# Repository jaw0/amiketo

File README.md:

tiny, low power, ARM-based board

* 35mm x 69mm
* breadboard friendly pinout

hardware:

* STM32F411
  * 96 MHz Cortex M4F
  * 100 uA / MHz
  * 10 analog inputs
  * 10 digital inputs
  * 10 digital outputs
  *  8 PWM outputs
  * i2c, spi, uart, usb
  * real-time-clock
  * board compat with most 48pin STM32s (eg. F103, L152, L072)
* micro SD card
* audio speaker
* OLED display
* AD5062 programmable battery charger
  * configurable charge current
  * configurable USB current
  * configurable charging parameters
* MAX17048 battery fuel gauge

software:

* can (will eventually) run open-source:
  * python
  * javascript
  * mbed
  * .NET
  * arduino
* comes with battery charger + data-logger
* write your own code

other:

* RoHS, lead-free
* fat-free, sugar-free, gluten-free

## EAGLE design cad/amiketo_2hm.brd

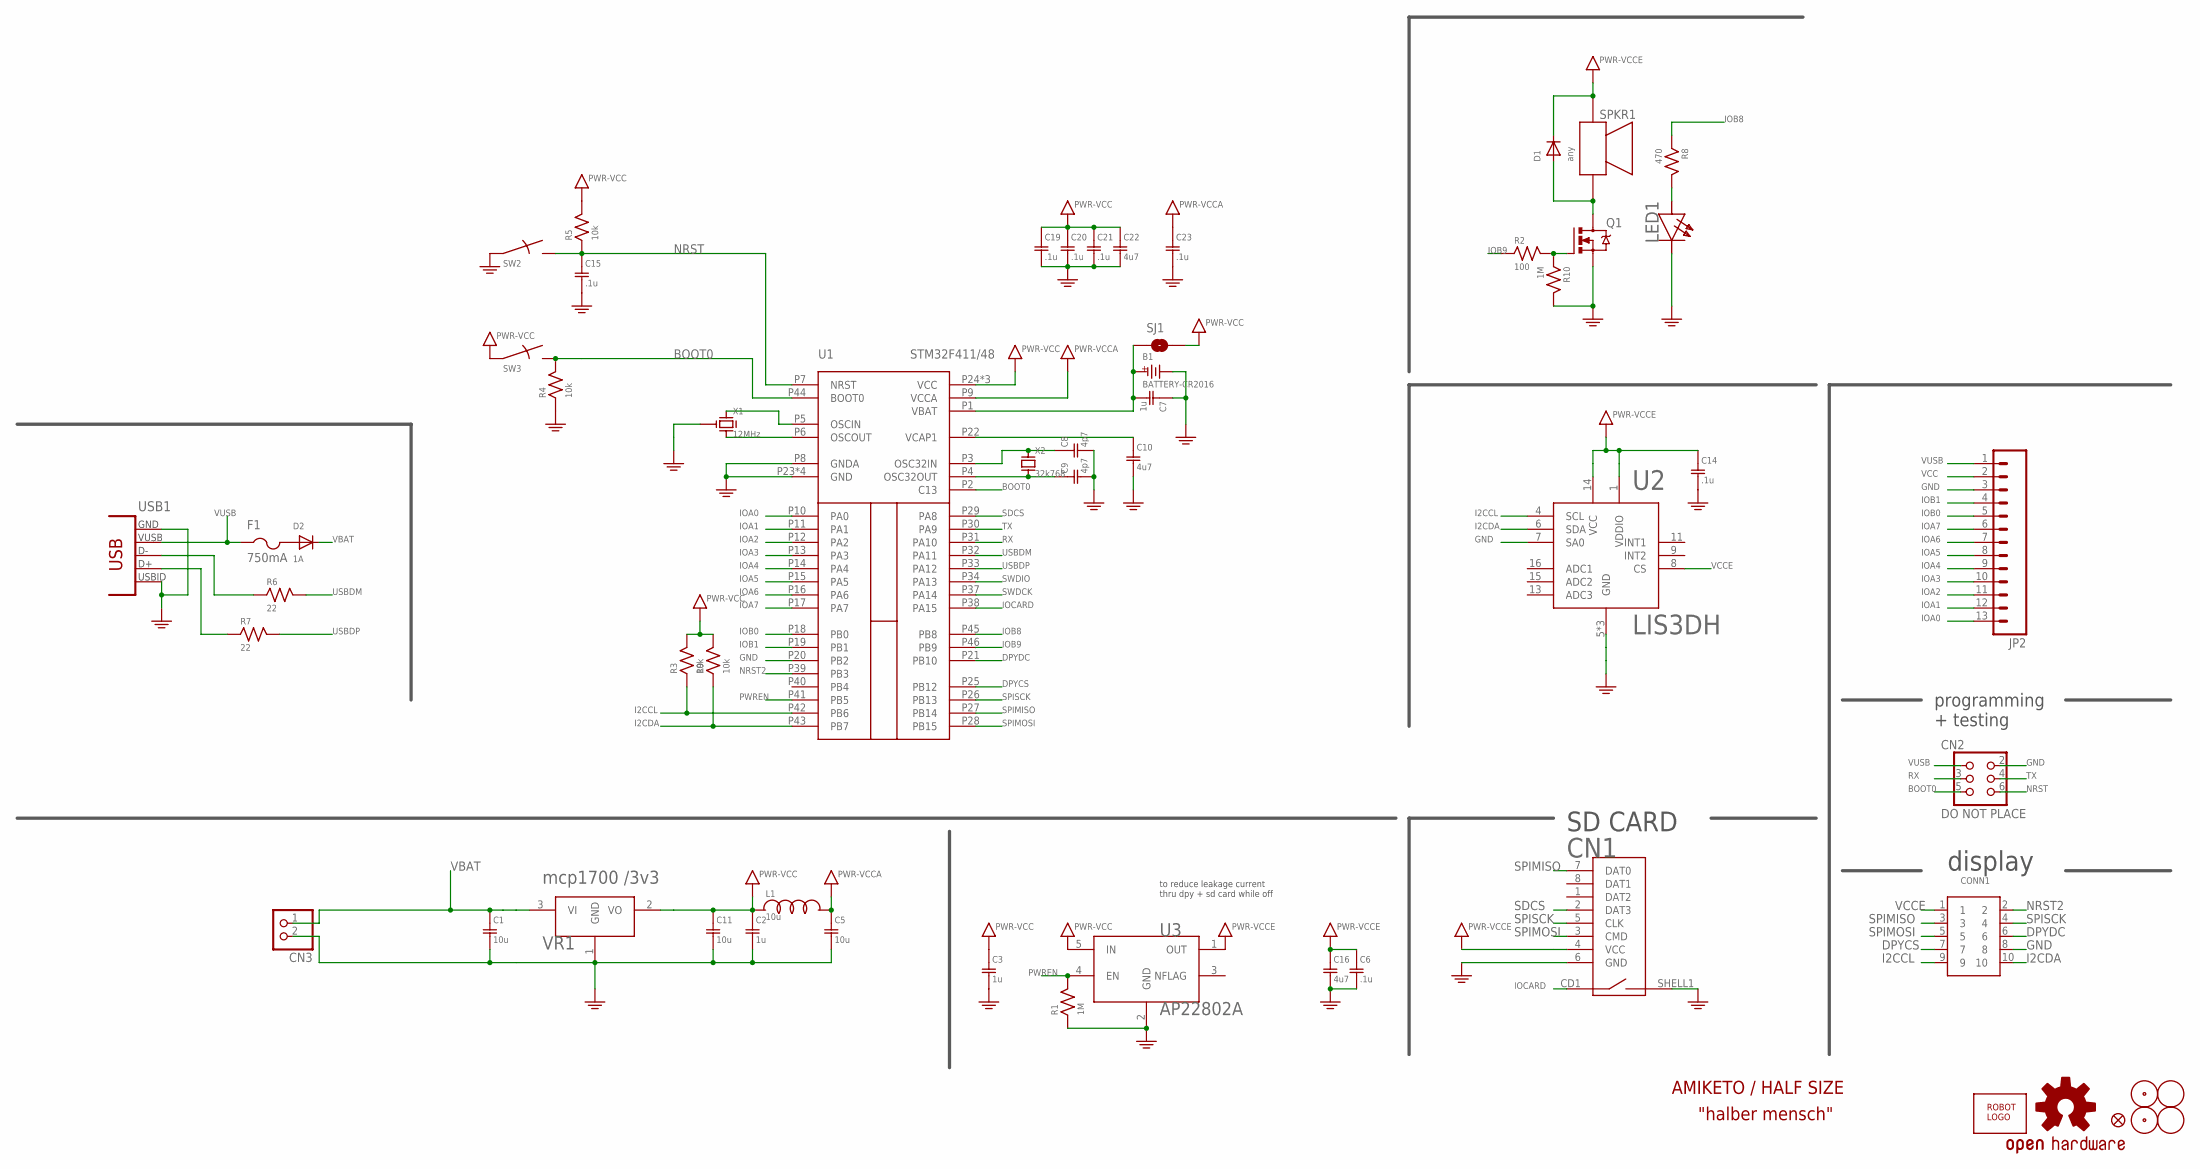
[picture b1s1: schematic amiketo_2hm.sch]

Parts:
B1: BATTERY-CR2016; CR1216
C1, C5, C11: 10u; SMD0603
C2, C3, C7: 1u; SMD0603
C6, C14, C15, C19, C20, C21, C23: .1u; SMD0603
C8, C9: 4p7; SMD0603
C10, C16, C22: 4u7; SMD0603
CN1: MICROSD-EJECT; MICROSD/EJECTOR
CN2: DO NOT PLACE; HEADER-3X2-POGO
CN3: JST_2PIN-SMT-RA; JST-PH-2-SMT-RA
CONN1: HEADER-5X2-PTH
D1: any; SMD0805D
D2: 1A; SMD0805D
F1: 750mA; SMD1206
JP2: M13; 1X13
L1: 10u; SMD0603
LED1: white; SMD0603D
LOGO1: OSHW-LOGOM; OSHW-LOGO-M
Q1: IRLML6344TRPBF; SOT-23
R1, R10: 1M; SMD0603
R2: 100; SMD0603
R3, R4, R5, R9: 10k; SMD0603
R6, R7: 22; SMD0603
R8: 470; SMD0603
SJ1: JUMPER-PAD-2-NOYES_SILK; PAD-JUMPER-2-NO_YES_SILK
SPKR1: PUI-5040; PUI-0540
SW2, SW3: SWITCHKMR211; KMR211
U1: STM32F411/48; UQPFN48
U2: LIS3DH; LGA16A
U3: AP22802A; SOT-23-5
U$1, U$5: FIDUCIAL
U$2, U$3: FIDUCIAL; FIDUCIAL_1MM
U$4: ROBOTMAN-LOGO2
U$6: FIDUCIALUFIDUCIAL; MICRO-FIDUCIAL
USB1: CON-USB-F-MICRO-B; CONN_USB_MICRO-B
VR1: mcp1700 /3v3; SOT-23-3
X1: 12MHz; RESONATOR-CSTCE
X2: 32k768; XTAL-32X15

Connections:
BOOT0: CN2.5, R4.2, SW3.2, SW3.4, U1.P2 (C13), U1.P44 (BOOT0)
DPYCS: CONN1.7, U1.P25 (PB12)
DPYDC: CONN1.6, U1.P21 (PB10)
GND: B1.MINUS (M), C1.2, C2.2, C3.2, C5.2, C6.2, C7.1, C8.2, C9.2, C10.2, C11.2, C14.2, C15.2, C16.2, C19.2, C20.2, C21.2, C22.2, C23.2, CN1.6 (GND), CN1.SHELL1 (SW2), CN2.2, CN3.2 (1), CONN1.8, JP2.3, LED1.C, Q1.2 (S), R1.1, R4.1, R10.2, SW2.1, SW2.3, U1.P8 (GNDA), U1.P20 (PB2), U1.P23 (GND), U1.P35 (GND), U1.P47 (GND), U1.PAD (GND), U2.5 (GND), U2.7 (SA0), U2.10 (GND), U2.12 (GND), U3.2 (GND), USB1.P4 (USBID), USB1.P5 (GND), VR1.1 (GND), X1.2 (G)
I2CCL: CONN1.9, R3.1, U1.P42 (PB6), U2.4 (SCL)
I2CDA: CONN1.10, R9.1, U1.P43 (PB7), U2.6 (SDA)
IOA0: JP2.13, U1.P10 (PA0)
IOA1: JP2.12, U1.P11 (PA1)
IOA2: JP2.11, U1.P12 (PA2)
IOA3: JP2.10, U1.P13 (PA3)
IOA4: JP2.9, U1.P14 (PA4)
IOA5: JP2.8, U1.P15 (PA5)
IOA6: JP2.7, U1.P16 (PA6)
IOA7: JP2.6, U1.P17 (PA7)
IOB0: JP2.5, U1.P18 (PB0)
IOB1: JP2.4, U1.P19 (PB1)
IOB8: R8.1, U1.P45 (PB8)
IOB9: R2.1, U1.P46 (PB9)
IOCARD: CN1.CD1 (SW1), U1.P38 (PA15)
unnamed: R6.1, USB1.P2 (D-)
unnamed: R7.1, USB1.P3 (D+)
unnamed: Q1.1 (G), R2.2, R10.1
unnamed: LED1.A, R8.2
unnamed: U1.P5 (OSCIN), X1.1 (X1)
unnamed: U1.P6 (OSCOUT), X1.3 (X2)
unnamed: D1.A, Q1.3 (D), SPKR1.P2
unnamed: C8.1, U1.P3 (OSC32IN), X2.P$1
unnamed: C9.1, U1.P4 (OSC32OUT), X2.P$2
unnamed: C10.1, U1.P22 (VCAP1)
unnamed: B1.PLUS1, B1.PLUS2, C7.2, SJ1.1, U1.P1 (VBAT)
unnamed: D2.A, F1.2
NRST: C15.1, CN2.6, R5.1, SW2.2, SW2.4, U1.P7 (NRST)
NRST2: CONN1.2, U1.P39 (PB3)
PWREN: R1.2, U1.P41 (PB5), U3.4 (EN)
RX: CN2.3, U1.P31 (PA10)
SDCS: CN1.2 (DAT3), U1.P29 (PA8)
SPIMISO: CN1.7 (DAT0), CONN1.3, U1.P27 (PB14)
SPIMOSI: CN1.3 (CMD), CONN1.5, U1.P28 (PB15)
SPISCK: CN1.5 (CLK), CONN1.4, U1.P26 (PB13)
SWDCK: U1.P37 (PA14)
SWDIO: U1.P34 (PA13)
TX: CN2.4, U1.P30 (PA9)
USBDM: R6.2, U1.P32 (PA11)
USBDP: R7.2, U1.P33 (PA12)
VBAT: C1.1, CN3.1 (2), D2.C, VR1.3 (VI)
VCC: C2.1, C3.1, C11.1, C19.1, C20.1, C21.1, C22.1, JP2.2, L1.1, R3.2, R5.2, R9.2, SJ1.2, SW3.1, SW3.3, U1.P24 (VCC), U1.P36 (VCC), U1.P48 (VCC), U3.5 (IN), VR1.2 (VO)
VCCA: C5.1, C23.1, L1.2, U1.P9 (VCCA)
VCCE: C6.1, C14.1, C16.1, CN1.4 (VCC), CONN1.1, D1.C, SPKR1.P1, U2.1 (VDDIO), U2.8 (CS), U2.14 (VCC), U3.1 (OUT)
VUSB: CN2.1, F1.1, JP2.1, USB1.P1 (VUSB)

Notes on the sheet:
SD CARD
display
to reduce leakage current thru dpy + sd card while off
programming + testing
AMIKETO / HALF SIZE
"halber mensch"

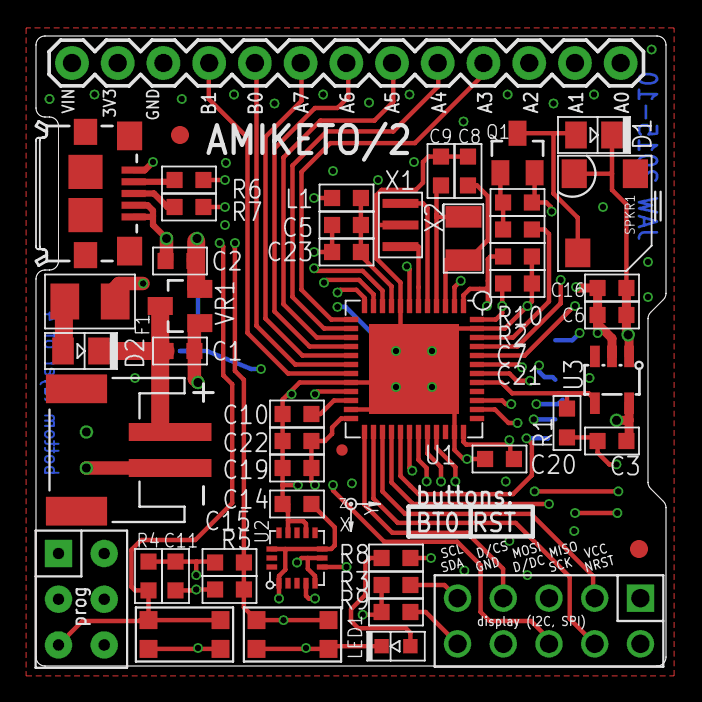
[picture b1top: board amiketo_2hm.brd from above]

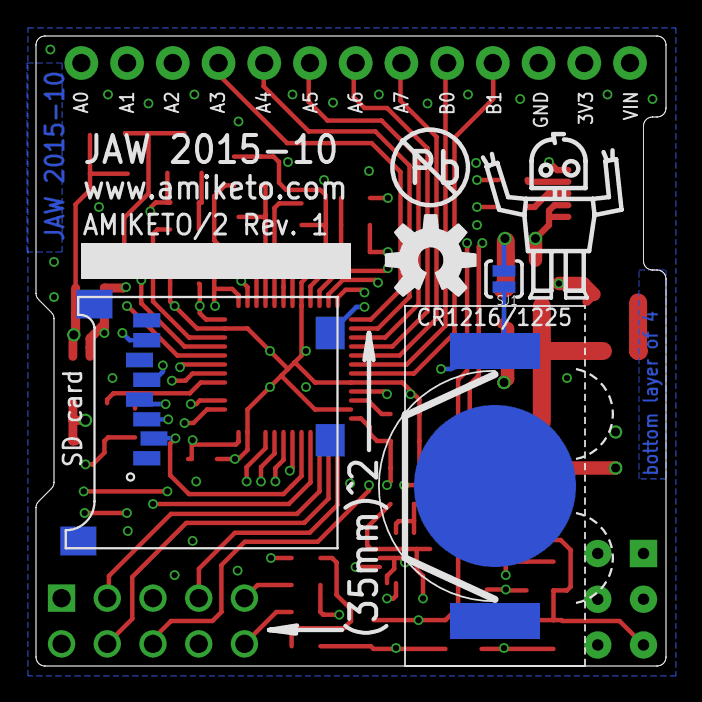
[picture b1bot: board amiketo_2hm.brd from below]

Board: 4 copper layers, 35.0 x 35.0 mm, 58 parts (7 on the bottom side), 47 nets.

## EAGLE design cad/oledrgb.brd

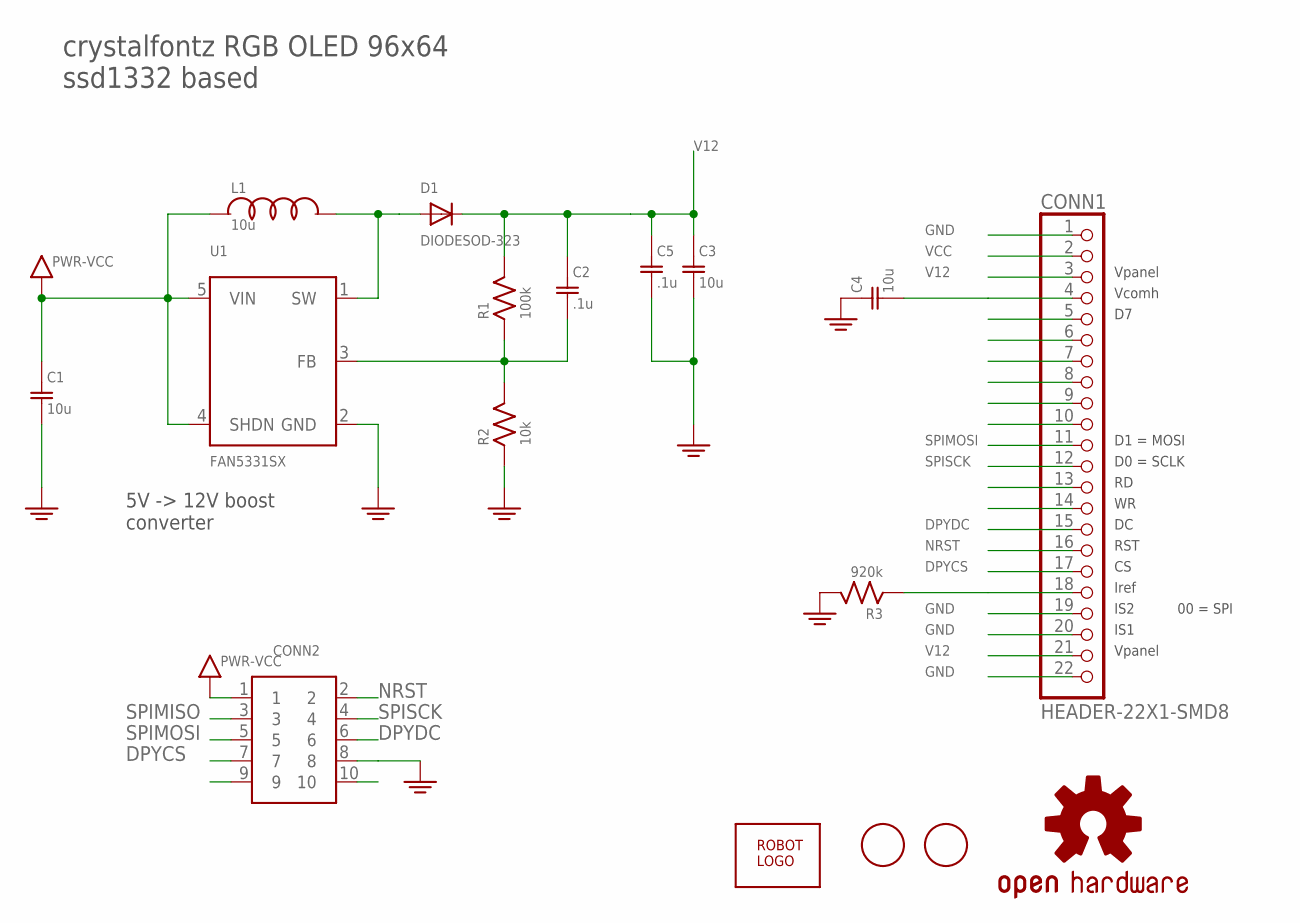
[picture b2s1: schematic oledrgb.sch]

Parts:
C1, C3, C4: 10u; SMD0603
C2, C5: .1u; SMD0603
CONN1: HEADER-22X1-SMD8
CONN2: HEADER-5X2-PTH
D1: DIODESOD-323; SOD-323
L1: 10u; SMD0603
LOGO1: OSHW-LOGOS; OSHW-LOGO-S
R1: 100k; SMD0603
R2: 10k; SMD0603
R3: 920k; SMD0603
U1: FAN5331SX; SOT23-5
U$1: ROBOTMAN-LOGO2
U$2, U$3: FIDUCIAL; FIDUCIAL_1MM

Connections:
DPYCS: CONN1.17, CONN2.7
DPYDC: CONN1.15, CONN2.6
GND: C1.2, C3.2, C4.1, C5.2, CONN1.1, CONN1.19, CONN1.20, CONN1.22, CONN2.8, R2.1, R3.2, U1.2 (GND)
unnamed: D1.A, L1.2, U1.1 (SW)
unnamed: C2.2, R1.1, R2.2, U1.3 (FB)
unnamed: C4.2, CONN1.4
unnamed: CONN1.18, R3.1
NRST: CONN1.16, CONN2.2
SPIMISO: CONN2.3
SPIMOSI: CONN1.11, CONN2.5
SPISCK: CONN1.12, CONN2.4
V12: C2.1, C3.1, C5.1, CONN1.3, CONN1.21, D1.C, R1.2
VCC: C1.1, CONN1.2, CONN2.1, L1.1, U1.4 (SHDN), U1.5 (VIN)

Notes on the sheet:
Vpanel
Vcomh
D0 = SCLK
D1 = MOSI
RST
Iref
IS2
IS1
00 = SPI
crystalfontz RGB OLED 96x64 ssd1332 based
5V -> 12V boost converter

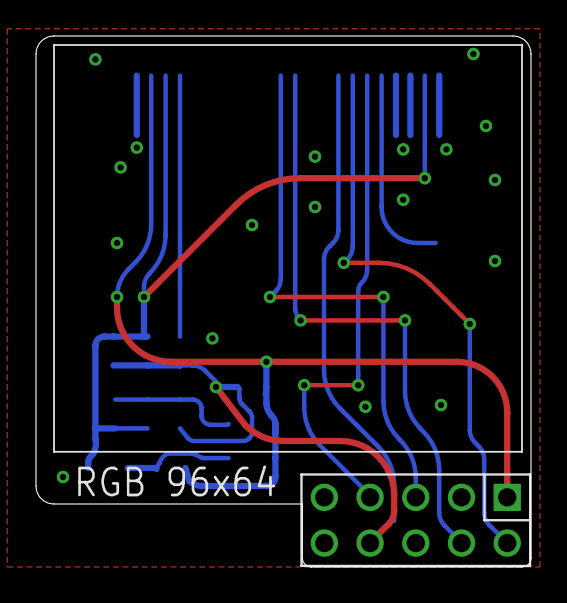
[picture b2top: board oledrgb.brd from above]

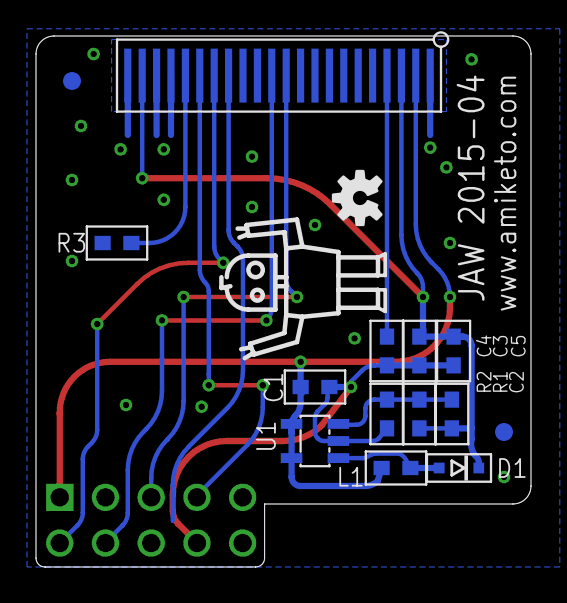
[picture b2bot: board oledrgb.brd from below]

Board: 2 copper layers, 27.5 x 29.5 mm, 17 parts (16 on the bottom side), 12 nets.

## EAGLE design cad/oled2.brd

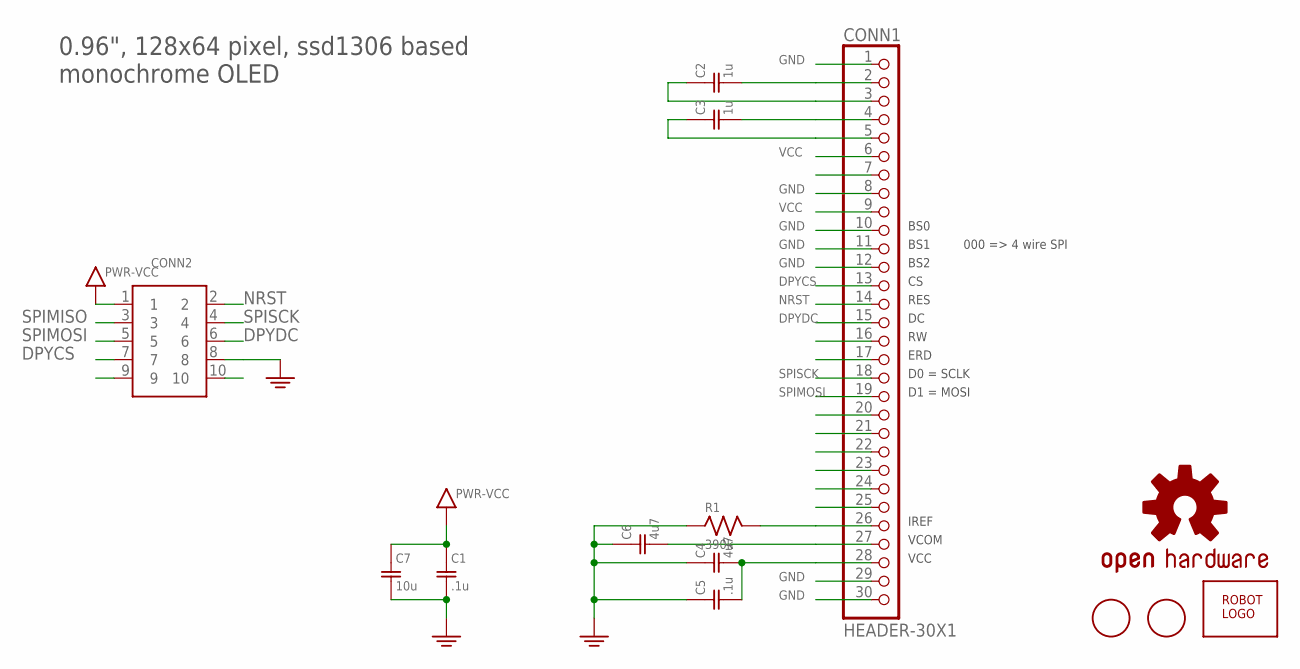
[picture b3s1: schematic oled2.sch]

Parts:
C1, C5: .1u; SMD0603
C2, C3: 1u; SMD0603
C4, C6: 4u7; SMD0603
C7: 10u; SMD0603
CONN1: HEADER-30X1; HEADER-30X1-SMD7
CONN2: HEADER-5X2-PTH
LOGO1: OSHW-LOGOS; OSHW-LOGO-S
R1: 390k; SMD0603
U$1, U$2: FIDUCIAL; FIDUCIAL_1MM
U$3: ROBOTMAN-LOGO2

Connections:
DPYCS: CONN1.13, CONN2.7
DPYDC: CONN1.15, CONN2.6
GND: C1.2, C4.1, C5.1, C6.1, C7.2, CONN1.1, CONN1.8, CONN1.10, CONN1.11, CONN1.12, CONN1.29, CONN1.30, CONN2.8, R1.1
unnamed: C2.2, CONN1.2
unnamed: C2.1, CONN1.3
unnamed: C3.2, CONN1.4
unnamed: C3.1, CONN1.5
unnamed: CONN1.26, R1.2
unnamed: C6.2, CONN1.27
unnamed: C4.2, C5.2, CONN1.28
NRST: CONN1.14, CONN2.2
SPIMISO: CONN2.3
SPIMOSI: CONN1.19, CONN2.5
SPISCK: CONN1.18, CONN2.4
VCC: C1.1, C7.1, CONN1.6, CONN1.9, CONN2.1

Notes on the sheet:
BS0
BS1
BS2
000 => 4 wire SPI
RES
ERD
D0 = SCLK
D1 = MOSI
IREF
VCOM
VCC
0.96", 128x64 pixel, ssd1306 based monochrome OLED

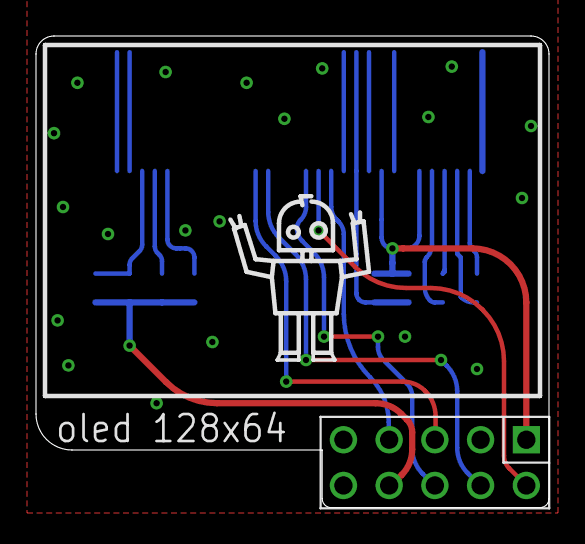
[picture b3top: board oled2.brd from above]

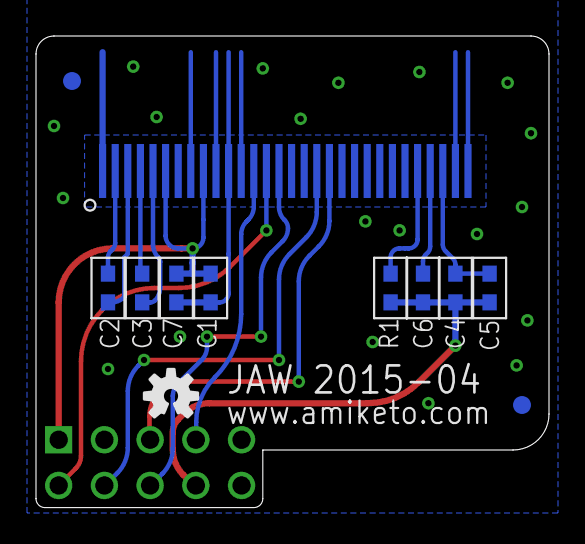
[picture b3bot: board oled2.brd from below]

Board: 2 copper layers, 28.5 x 26.2 mm, 14 parts (12 on the bottom side), 14 nets.

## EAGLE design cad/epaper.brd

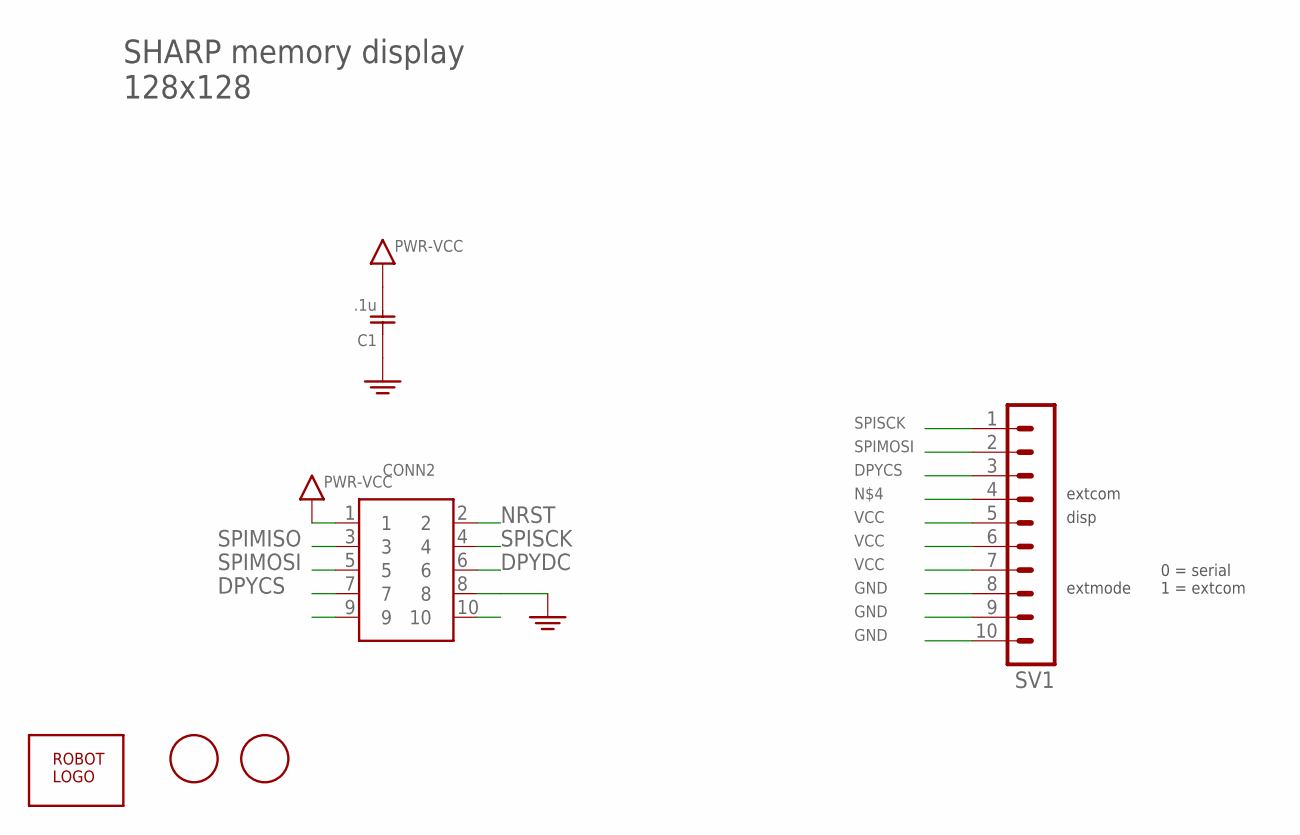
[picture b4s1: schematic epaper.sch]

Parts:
C1: .1u; SMD0603
CONN2: HEADER-5X2-PTH
SV1: MA10-1-M05/FFC; M05-1X10-RA
U$1: ROBOTMAN-LOGO2
U$2, U$3: FIDUCIAL; FIDUCIAL_1MM

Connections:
DPYCS: CONN2.7, SV1.3
DPYDC: CONN2.6
GND: C1.1, CONN2.8, SV1.8, SV1.9, SV1.10
NRST: CONN2.2
SPIMISO: CONN2.3
SPIMOSI: CONN2.5, SV1.2
SPISCK: CONN2.4, SV1.1
VCC: C1.2, CONN2.1, SV1.5, SV1.6, SV1.7

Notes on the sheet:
SHARP memory display 128x128
extcom
extmode
disp
0 = serial 1 = extcom

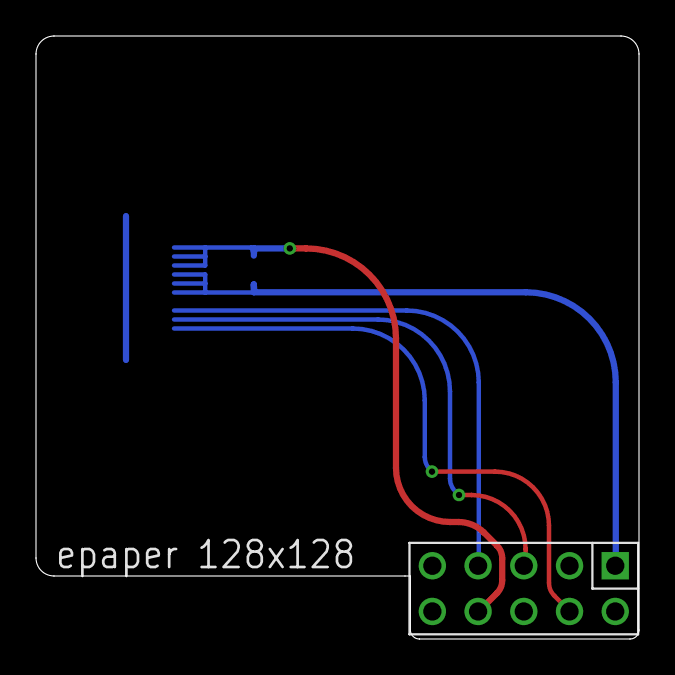
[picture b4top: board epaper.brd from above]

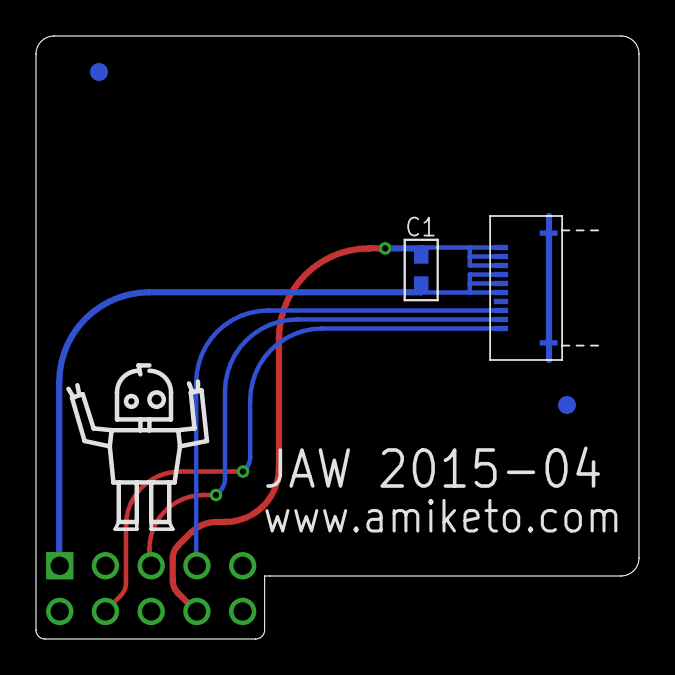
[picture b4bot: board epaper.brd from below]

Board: 2 copper layers, 33.5 x 33.5 mm, 6 parts (5 on the bottom side), 5 nets.

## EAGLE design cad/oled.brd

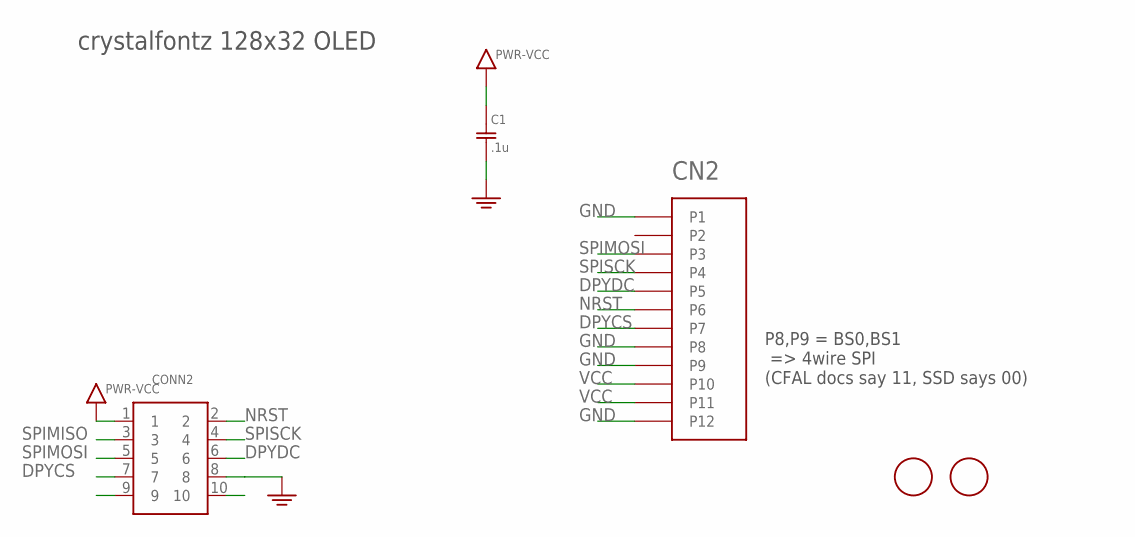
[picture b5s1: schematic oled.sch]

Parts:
C1: .1u; SMD0603
CN2: MA12-1; M05-1X12-RA
CONN2: HEADER-5X2-PTH
U$1, U$2: FIDUCIAL; FIDUCIAL_1MM

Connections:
DPYCS: CN2.P7, CONN2.7
DPYDC: CN2.P5, CONN2.6
GND: C1.2, CN2.P1, CN2.P8, CN2.P9, CN2.P12, CONN2.8
NRST: CN2.P6, CONN2.2
SPIMISO: CONN2.3
SPIMOSI: CN2.P3, CONN2.5
SPISCK: CN2.P4, CONN2.4
VCC: C1.1, CN2.P10, CN2.P11, CONN2.1

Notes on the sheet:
P8,P9 = BS0,BS1 => 4wire SPI (CFAL docs say 11, SSD says 00)
crystalfontz 128x32 OLED

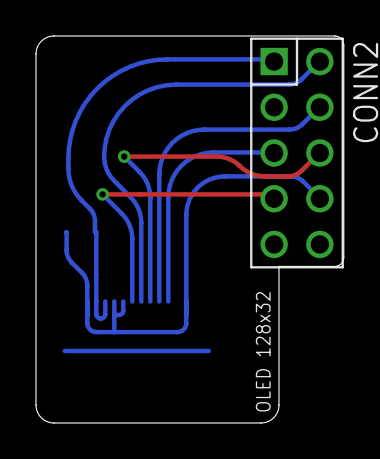
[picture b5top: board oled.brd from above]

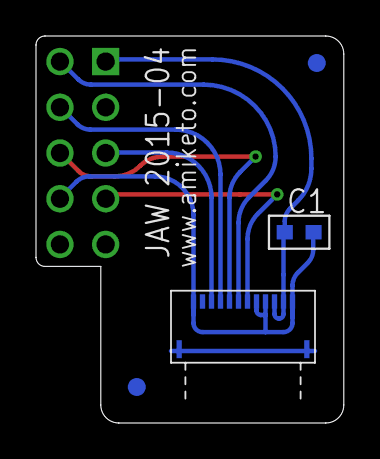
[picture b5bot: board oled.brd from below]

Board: 2 copper layers, 17.1 x 21.5 mm, 5 parts (4 on the bottom side), 7 nets.

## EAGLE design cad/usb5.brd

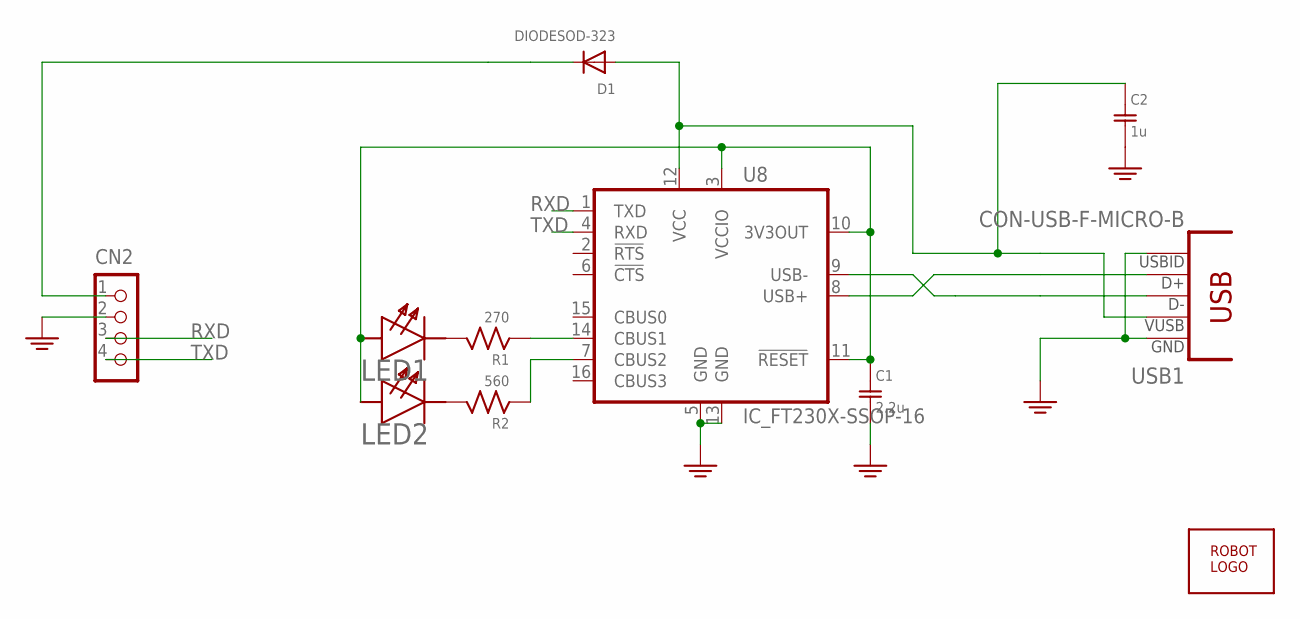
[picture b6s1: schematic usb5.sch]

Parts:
C1: 2.2u; SMD0603
C2: 1u; SMD0603
CN2: CON_HEADER_1X04; M1X4
D1: DIODESOD-323; SOD-323
LED1: GREEN; SMD0603D
LED2: ORANGE; SMD0603D
R1: 270; SMD0603
R2: 560; SMD0603
U8: IC_FT230X-SSOP-16; SSOP-16-FTDI
U$1: ROBOTMAN-LOGO2
USB1: CON-USB-F-MICRO-B; CONN_USB_MICRO-B

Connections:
GND: C1.2, C2.2, CN2.2, U8.5 (GND), U8.13 (GND), USB1.P4 (USBID), USB1.P5 (GND)
unnamed: CN2.1, D1.C
unnamed: U8.8 (USB+), USB1.P3 (D+)
unnamed: U8.9 (USB-), USB1.P2 (D-)
unnamed: LED1.C, R1.2
unnamed: LED2.C, R2.2
unnamed: R1.1, U8.14 (CBUS1)
unnamed: R2.1, U8.7 (CBUS2)
RXD: CN2.3, U8.1 (TXD)
TXD: CN2.4, U8.4 (RXD)
USB3V3: C1.1, LED1.A, LED2.A, U8.3 (VCCIO), U8.10 (3V3OUT), U8.11 (!RESET)
VBUS: C2.1, D1.A, U8.12 (VCC), USB1.P1 (VUSB)

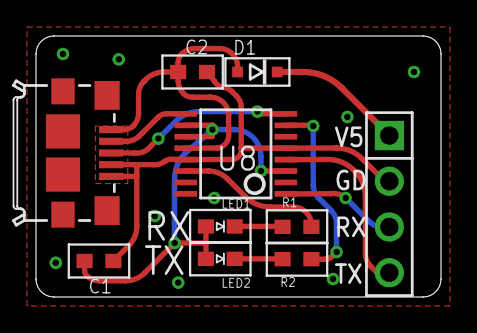
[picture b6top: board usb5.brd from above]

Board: 2 copper layers, 22.5 x 14.5 mm, 11 parts (1 on the bottom side), 12 nets.

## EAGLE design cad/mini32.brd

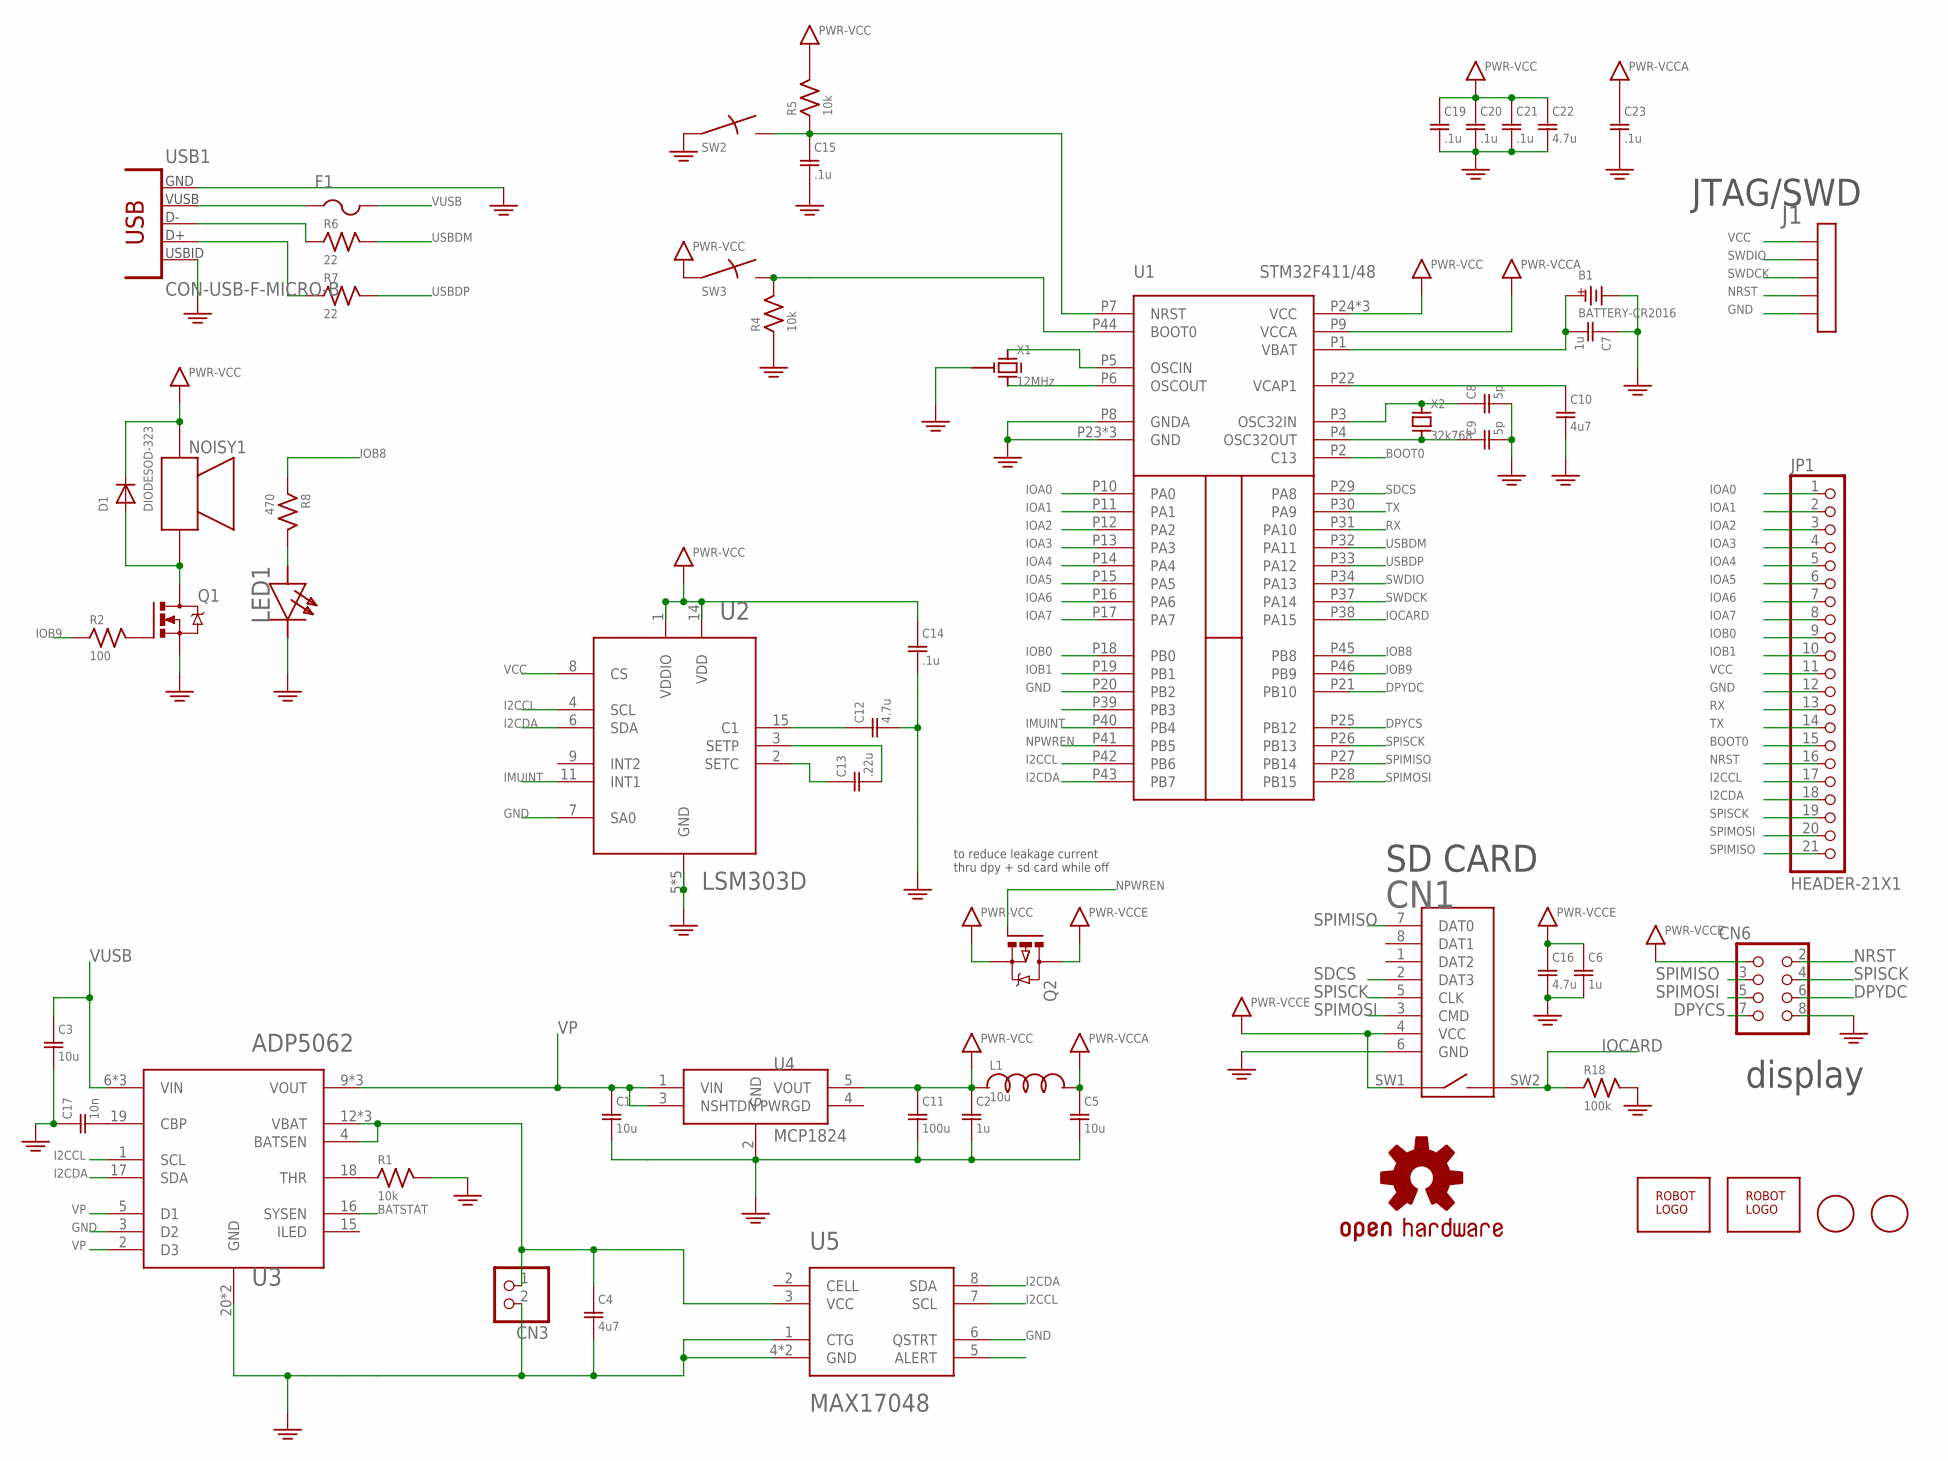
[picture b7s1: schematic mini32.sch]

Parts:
B1: BATTERY-CR2016; CR1216
C1, C3, C5: 10u; SMD0603
C2, C6, C7: 1u; SMD0603
C4, C10: 4u7; SMD0603
C8, C9: 5p; SMD0603
C11: 100u; SMD1210
C12, C16, C22: 4.7u; SMD0603
C13: .22u; SMD0603
C14, C15, C19, C20, C21, C23: .1u; SMD0603
C17: 10n; SMD0603
CN1: MICROSDPLAIN; MICROSD/MOLEX/FRONT/PLAIN
CN3: JST_2PIN-SMT-RA; JST-PH-2-SMT-RA
CN6: HEADER-2X4; HEADER-2X04
D1: DIODESOD-323; SOD-323
F1: PTCFUSE-1206; R1206
J1: HEADER-5X1; M127-5X1
JP1: HEADER-21X1; HEADER-21X1-PTH
L1: 10u; SMD0603
LED1: white; SMD0603D
LOGO1: OSHW-LOGOM; OSHW-LOGO-M
NOISY1: PUI-5040; PUI-0540
Q1: IRLML6344TRPBF; SOT-23
Q2: DMP2035U-7; SOT-23
R1, R4, R5: 10k; SMD0603
R2: 100; SMD0603
R6, R7: 22; SMD0603
R8: 470; SMD0603
R18: 100k; SMD0603
SW2, SW3: SWITCHKMR211; KMR211
U1: STM32F411/48; UQPFN48
U2: LSM303D; LGA16A
U3: ADP5062; LGA20P
U4: MCP1824; SOT-23-5
U5: MAX17048; TDFN8EP
U$1, U$4: ROBOTMAN-LOGO2
U$2, U$3: FIDUCIAL; FIDUCIAL_1MM
USB1: CON-USB-F-MICRO-B; CONN_USB_MICRO-B
X1: 12MHz; RESONATOR-CSTCE
X2: 32k768; XTAL-32X15

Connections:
BATSTAT: U3.16 (SYSEN)
BOOT0: JP1.15, R4.2, SW3.2, SW3.4, U1.P2 (C13), U1.P44 (BOOT0)
DPYCS: CN6.7, U1.P25 (PB12)
DPYDC: CN6.6, U1.P21 (PB10)
GND: B1.MINUS (M), C1.2, C2.2, C3.2, C4.2, C5.2, C6.2, C7.1, C8.2, C9.2, C10.2, C11.2, C12.2, C14.2, C15.2, C16.2, C17.1, C19.2, C20.2, C21.2, C22.2, C23.2, CN1.6 (GND), CN3.2 (1), CN6.8, J1.P$5 (5), JP1.12, LED1.C, Q1.2 (S), R1.2, R4.1, R18.2, SW2.1, SW2.3, U1.P8 (GNDA), U1.P20 (PB2), U1.P23 (GND), U1.P35 (GND), U1.P47 (GND), U2.5 (GND), U2.7 (SA0), U2.10 (GND), U2.12 (GND), U2.13 (GND), U2.16 (GND), U3.3 (D2), U3.20 (GND), U3.PAD (GND), U4.2 (GND), U5.1 (CTG), U5.4 (GND), U5.6 (QSTRT), U5.PAD (GND), USB1.P4 (USBID), USB1.P5 (GND), X1.2 (G)
I2CCL: JP1.17, U1.P42 (PB6), U2.4 (SCL), U3.1 (SCL), U5.7 (SCL)
I2CDA: JP1.18, U1.P43 (PB7), U2.6 (SDA), U3.17 (SDA), U5.8 (SDA)
IMUINT: U1.P40 (PB4), U2.11 (INT1)
IOA0: JP1.1, U1.P10 (PA0)
IOA1: JP1.2, U1.P11 (PA1)
IOA2: JP1.3, U1.P12 (PA2)
IOA3: JP1.4, U1.P13 (PA3)
IOA4: JP1.5, U1.P14 (PA4)
IOA5: JP1.6, U1.P15 (PA5)
IOA6: JP1.7, U1.P16 (PA6)
IOA7: JP1.8, U1.P17 (PA7)
IOB0: JP1.9, U1.P18 (PB0)
IOB1: JP1.10, U1.P19 (PB1)
IOB8: R8.1, U1.P45 (PB8)
IOB9: R2.1, U1.P46 (PB9)
IOCARD: CN1.SW2, R18.1, U1.P38 (PA15)
unnamed: C12.1, U2.15 (C1)
unnamed: C13.2, U2.3 (SETP)
unnamed: F1.1, USB1.P1 (VUSB)
unnamed: C13.1, U2.2 (SETC)
unnamed: C17.2, U3.19 (CBP)
unnamed: R1.1, U3.18 (THR)
unnamed: R6.1, USB1.P2 (D-)
unnamed: R7.1, USB1.P3 (D+)
unnamed: Q1.1 (G), R2.2
unnamed: LED1.A, R8.2
unnamed: U1.P5 (OSCIN), X1.1 (X1)
unnamed: U1.P6 (OSCOUT), X1.3 (X2)
unnamed: D1.A, NOISY1.P2, Q1.3 (D)
unnamed: C8.1, U1.P3 (OSC32IN), X2.P$1
unnamed: C9.1, U1.P4 (OSC32OUT), X2.P$2
unnamed: C10.1, U1.P22 (VCAP1)
unnamed: B1.PLUS1, B1.PLUS2, C7.2, U1.P1 (VBAT)
NPWREN: Q2.1 (G), U1.P41 (PB5)
NRST: C15.1, CN6.2, J1.P$4 (4), JP1.16, R5.1, SW2.2, SW2.4, U1.P7 (NRST)
RX: JP1.13, U1.P31 (PA10)
SDCS: CN1.2 (DAT3), U1.P29 (PA8)
SPIMISO: CN1.7 (DAT0), CN6.3, JP1.21, U1.P27 (PB14)
SPIMOSI: CN1.3 (CMD), CN6.5, JP1.20, U1.P28 (PB15)
SPISCK: CN1.5 (CLK), CN6.4, JP1.19, U1.P26 (PB13)
SWDCK: J1.P$3 (3), U1.P37 (PA14)
SWDIO: J1.P$2 (2), U1.P34 (PA13)
SWDWO: U1.P39 (PB3)
TX: JP1.14, U1.P30 (PA9)
USBDM: R6.2, U1.P32 (PA11)
USBDP: R7.2, U1.P33 (PA12)
VBAT: C4.1, CN3.1 (2), U3.4 (BATSEN), U3.12 (VBAT), U3.13 (VBAT), U3.14 (VBAT), U5.3 (VCC)
VCC: C2.1, C11.1, C14.1, C19.1, C20.1, C21.1, C22.1, D1.C, J1.P$1 (1), JP1.11, L1.1, NOISY1.P1, Q2.2 (S), R5.2, SW3.1, SW3.3, U1.P24 (VCC), U1.P36 (VCC), U1.P48 (VCC), U2.1 (VDDIO), U2.8 (CS), U2.14 (VDD), U4.5 (VOUT)
VCCA: C5.1, C23.1, L1.2, U1.P9 (VCCA)
VCCE: C6.1, C16.1, CN1.4 (VCC), CN1.SW1, CN6.1, Q2.3 (D)
VP: C1.1, U3.2 (D3), U3.5 (D1), U3.9 (VOUT), U3.10 (VOUT), U3.11 (VOUT), U4.1 (VIN), U4.3 (NSHTDN)
VUSB: C3.1, F1.2, U3.6 (VIN), U3.7 (VIN), U3.8 (VIN)

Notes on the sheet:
SD CARD
display
JTAG/SWD
to reduce leakage current thru dpy + sd card while off

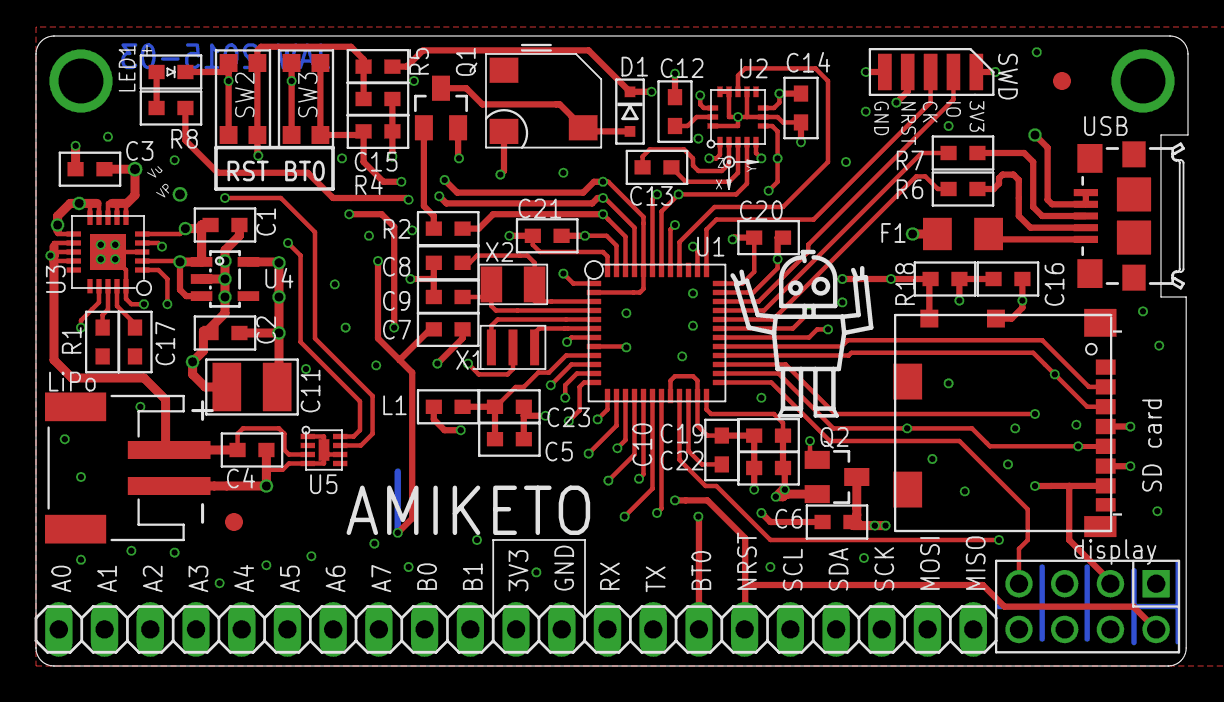
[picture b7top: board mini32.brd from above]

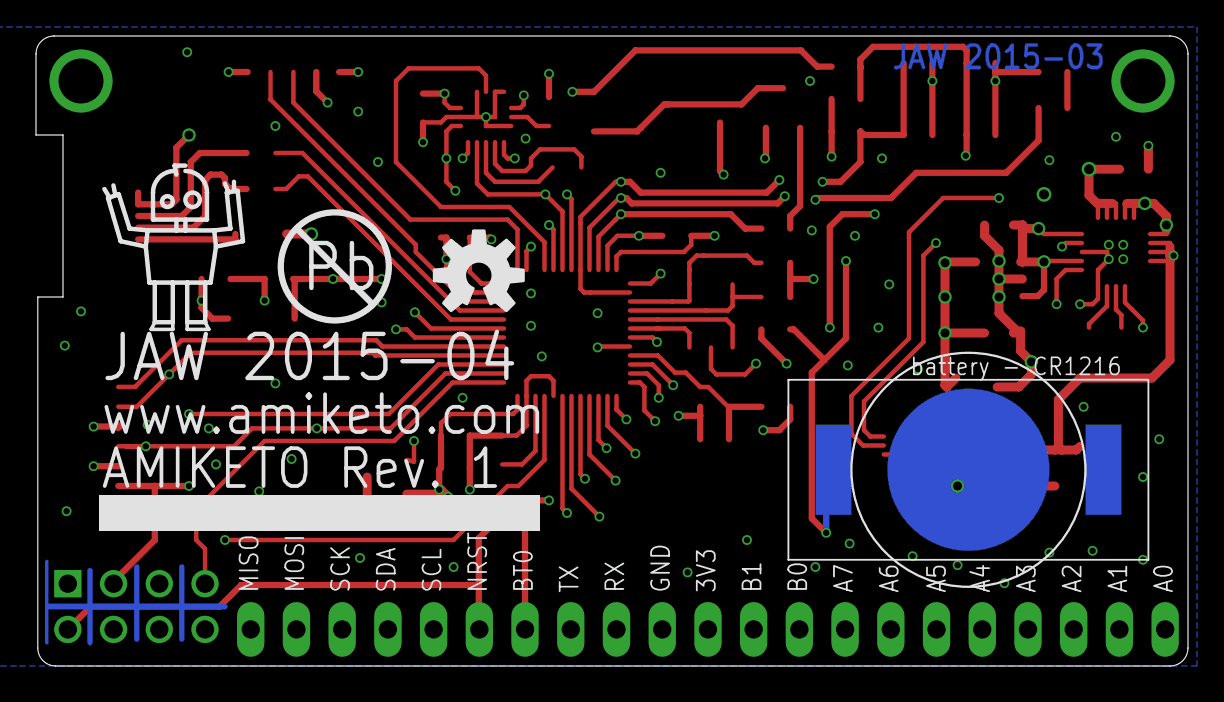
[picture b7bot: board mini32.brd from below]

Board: 4 copper layers, 64.0 x 35.0 mm, 58 parts (3 on the bottom side), 55 nets.

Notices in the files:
parts and their libraries:
Sparkfun-Aesthetics: Licensing: Creative Commons ShareAlike 4.0 International - https://creativecommons.org/licenses/by-sa/4.0
